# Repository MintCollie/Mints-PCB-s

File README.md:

# Mint test pcb
This repo is my attempt at creating pcb's, mainly keyboards. 
https://docs.google.com/document/d/1RwrXNXQGxuRLmxqcRp_Vr_PNWWCWalhN9jxpf7pPvLY/edit?usp=sharing

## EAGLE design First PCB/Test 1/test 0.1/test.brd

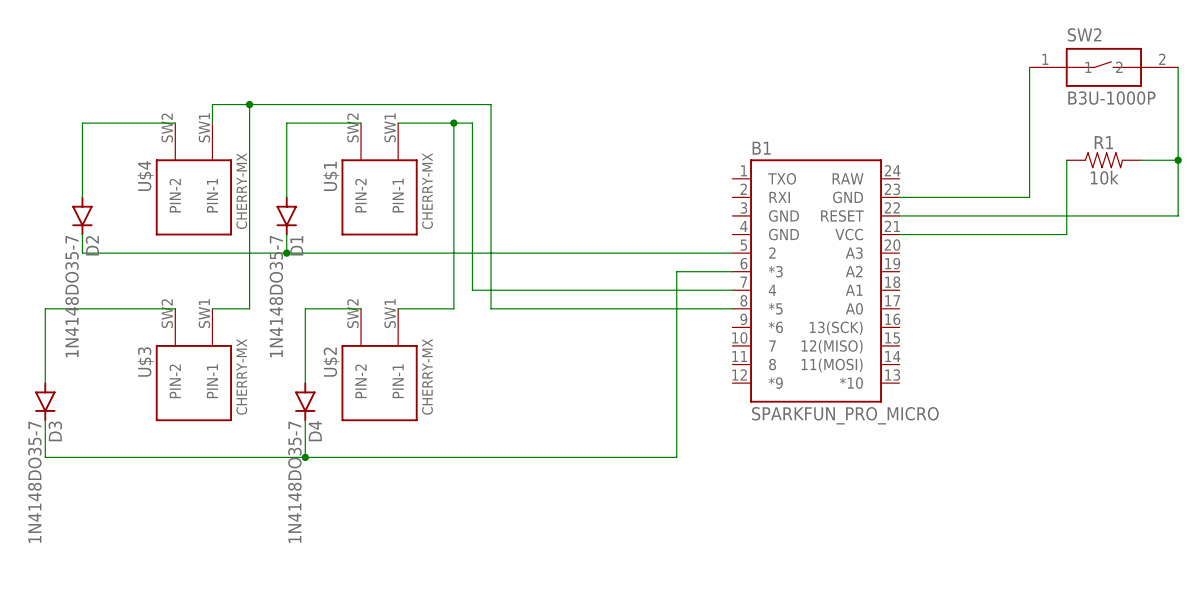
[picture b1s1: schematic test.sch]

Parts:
B1: SPARKFUN_PRO_MICRO
D1, D2, D3, D4: 1N4148DO35-7; DO35-7
R1: 10k; 0402; MPN MCWR06X1002FTL
SW2: B3U-1000P
U$1, U$2, U$3, U$4: CHERRY-MX

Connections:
GND: B1.3 (GND), B1.4 (GND)
unnamed: B1.22 (RESET), R1.2, SW2.2
unnamed: B1.21 (VCC), R1.1
unnamed: B1.23 (GND), SW2.1
unnamed: B1.5 (2), D1.C, D2.C
unnamed: D1.A, U$1.SW2 (PIN-2)
unnamed: B1.7 (4), U$1.SW1 (PIN-1), U$2.SW1 (PIN-1)
unnamed: B1.6 (*3), D3.C, D4.C
unnamed: D2.A, U$4.SW2 (PIN-2)
unnamed: B1.8 (*5), U$3.SW1 (PIN-1), U$4.SW1 (PIN-1)
unnamed: D4.A, U$2.SW2 (PIN-2)
unnamed: D3.A, U$3.SW2 (PIN-2)
RAW: B1.24 (RAW)

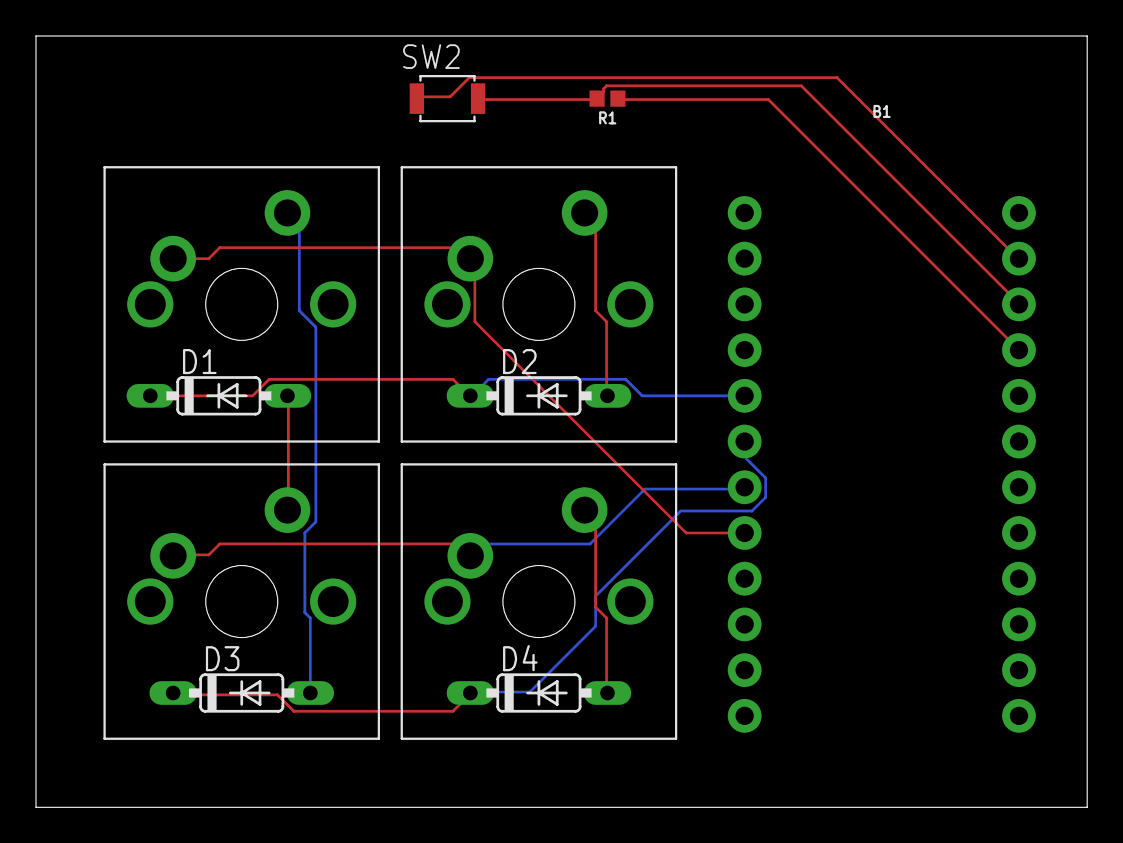
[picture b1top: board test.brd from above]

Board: 2 copper layers, 58.4 x 42.9 mm, 11 parts (0 on the bottom side), 12 nets.

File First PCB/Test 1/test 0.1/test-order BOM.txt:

Order list for C:/Users/Mint/Documents/EAGLE/projects/Learning/First PCB/Test 1/test 0.1/test.sch
Exported from EAGLE with DesignLink

Quantity	Value	Package	Order code	Manufacturer	Manuf. Code	Availability	Price (from)	Description
1	SPARKFUN_PRO_MICRO	SPARKFUN_PRO_MICRO	unknown					
2	1N4148DO35-7	DO35-7	unknown					
2	CHERRY-MX-DIODE	CHERRY-MX-DIODE	unknown					
1	10k	0402	94X1379		MCWR06X1002FTL	299994	0.011	MULTICOMP - MCWR06X1002FTL - SURFACE MOUNT THICK FILM RESISTOR, MCWR SERIES ROHS COMPLIANT: YES
1	B3U-1000P	B3U-1000P	78M0188		B3U-1000P	1485	0.526	OMRON ELECTRONIC COMPONENTS - B3U-1000P - TACTILE SWITCH, SPST-NO, 0.05A, SMD

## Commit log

2019-06-03 added starting files
2019-06-03 error fixing submodules
2019-08-14 removed KiCAD submodules, switching to EAGLE
2019-08-14 Added EAGLE lib for mx footprint and arduino pro micro(sparkfun contains lots of extras)
2019-08-14 moved old KiCAD files into folder
2019-08-14 added first project
2019-08-14 added first schematic with pro micro 1 switch with diode and one switch with LED
2019-08-14 added reset switch to schematic
2019-08-14 added two key switches with diodes
2019-08-14 Finished for the night. Completed board to finished status and added text + qr. Tested upload to oshpark but qr code did not show up.
2019-08-15 Added QR code to bottom layer, Need to resize. Need to fix diode route and then submit for review
2019-08-15 Update README.md
    Changed link to my google doc on all data I have
2019-08-19 slight changes to board layout need to finish still
2019-08-19 quick file save to match question for geekhack
2019-08-20 finished board and submitted for review, https://geekhack.org/index.php?topic=102077.0

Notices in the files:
parts and their libraries:
SparkFun-Boards: Licensing: Creative Commons ShareAlike 4.0 International - https://creativecommons.org/licenses/by-sa/4.0
